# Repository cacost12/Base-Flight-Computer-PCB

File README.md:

<h1>Flight Computer Lite</h1>

<p><b>Current PCB Revision:</b> 1.0</p>
<p><b>PCB Part Number:</b> A0007</p>

<p>The Avionics team aims to produce a dual-deploy flight computer 
 for use in high powered rocketry projects. The Avionics
flight computer PCB uses an ARM Microcontroller to provide a 
computationally capable embedded protoyping 
platform for high powered rocketry projects with minimal wiring and a small
 form factor.</p>

<b>Working Directory Structure:</b>
 
 <p>
doc: documentation
    
src: source design files, e.g. schematic and board files
 
lib: libraries for schematic symbols and footprints
 
production: files needed for pcb fabrication, e.g. gerbers, profile, drill file
 
 sim: simulation files 
  
 cad: 3d models
   
 img: images of circuit/footprints for github display 
 </p>

<h2>3D Model: </h2>

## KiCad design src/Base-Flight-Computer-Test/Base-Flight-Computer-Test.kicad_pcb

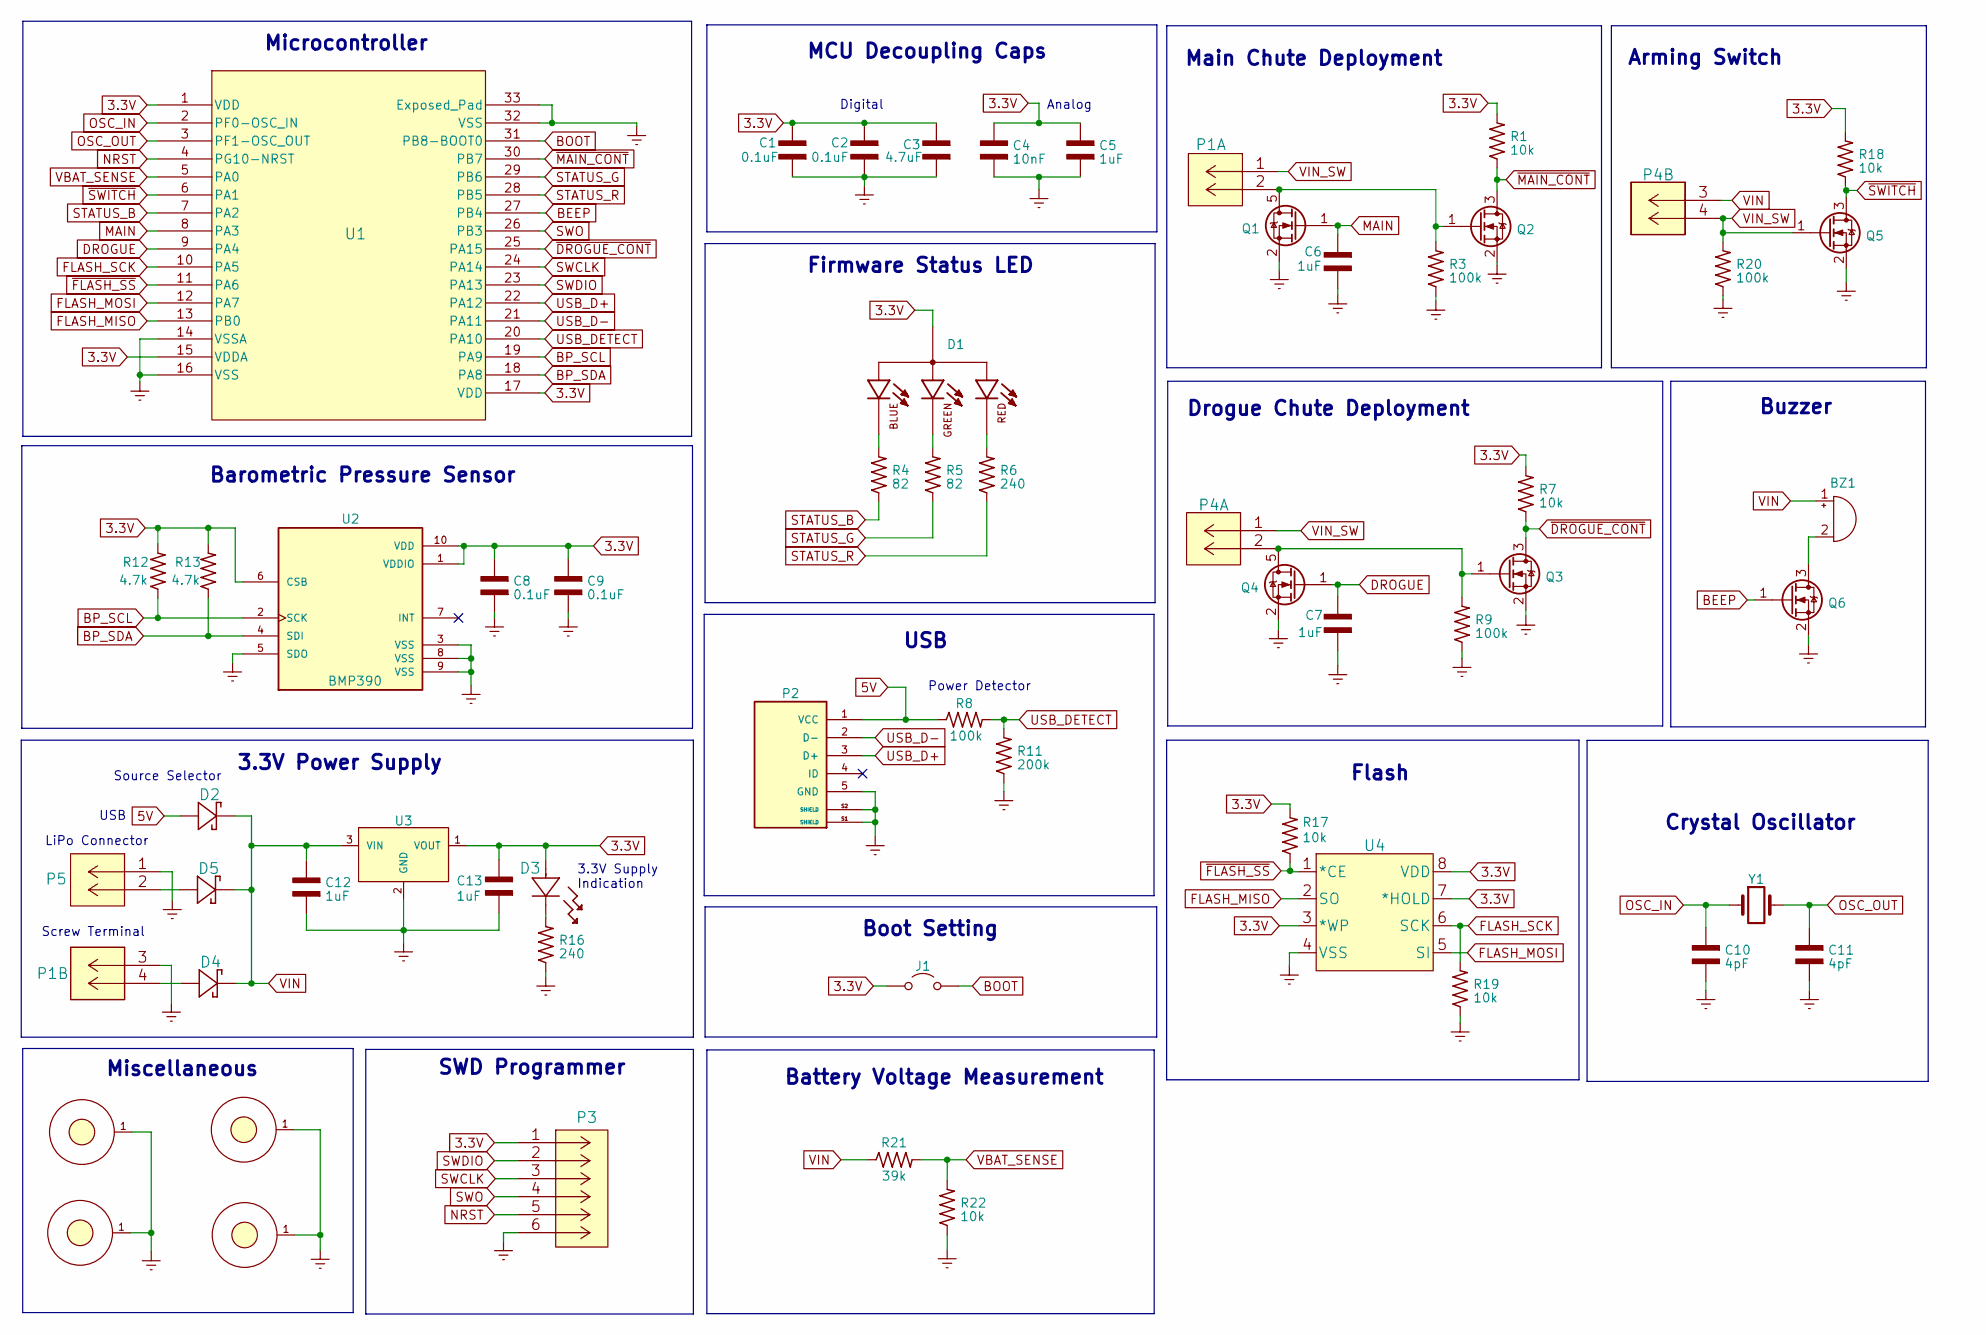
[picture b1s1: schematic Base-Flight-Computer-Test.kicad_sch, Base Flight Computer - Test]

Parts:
BZ1: AT-1438-TWT-R
C1, C2, C8, C9: 0.1uF; CAP_0402
C3: 4.7uF; CAP_0402
C4: 10nF; CAP_0402
C5, C6, C7: 1uF; CAP_0402
C10, C11: 4pF; CAP_0402
C12, C13: 1uF; CAP_0603
D1: CLMVC-FKA-CL1D1L71BB7C3C3
D2, D4, D5: PMEG3010AESBYL
D3: LTST-C191KGKT
H1, H2, H3, H4: Mounting-Hole-4-40; MountingHole_4-40
J1: Jumper_NO; Jumper-NO
P1, P4: 1984659; 1546551-4
P2: USB; 10118194-0001LF
P3: 0530470610; 53047-0610
P5: B2B-PH-K-SLFSN_JST
Q1, Q4: QS5U17TR
Q2, Q3, Q5, Q6: 2N7002W-7-F
R1, R7, R17, R18, R19, R22: 10k; RES_0402
R3, R8, R9, R20: 100k; RES_0402
R4, R5: 82; RES_0402
R6, R16: 240; RES_0402
R11: 200k; RES_0402
R12, R13: 4.7k; RES_0402
R21: 39k; RES_0402
U1: STM32G4A1KEU6
U2: BMP390
U3: LMS8117AMP-3.3_NOPB; AP7370-33Y-13
U4: SST25VF040B-50-4I-S2AE-T
Y1: ECS-240-18-33-JGN-TR; ECS-240-12-37B-CKY-TR

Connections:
3.3V: C1.1, C2.1, C3.1, C4.1, C5.1, C8.1, C9.1, C13.1, D1.1, D3.2, J1.1 (A), P3.1, R1.2, R7.2, R12.2, R13.2, R17.2, R18.2, U1.1 (VDD), U1.15 (VDDA), U1.17 (VDD), U2.1 (VDDIO), U2.6 (CSB), U2.10 (VDD), U3.1 (VOUT), U4.3 (*WP), U4.7 (*HOLD), U4.8 (VDD)
5V: D2.A, P2.1 (VCC), R8.1
BEEP: Q6.1 (G), U1.27 (PB4)
BOOT: J1.2 (B), U1.31 (PB8-BOOT0)
BP_SCL: R12.1, U1.19 (PA9), U2.2 (SCK)
BP_SDA: R13.1, U1.18 (PA8), U2.4 (SDI)
DROGUE: C7.1, Q4.1 (G), U1.9 (PA4)
Earth: C1.2, C2.2, C3.2, C4.2, C5.2, C6.2, C7.2, C8.2, C9.2, C10.2, C11.2, C12.2, C13.2, H1.1, H2.1, H3.1, H4.1, P1.3 (5), P2.5 (GND), P2.S1 (SHIELD), P2.S2 (SHIELD), P3.6, P5.1 (5), Q1.2 (S), Q2.2 (S), Q3.2 (S), Q4.2 (S), Q5.2 (S), Q6.2 (S), R3.1, R9.1, R11.1, R16.1, R19.1, R20.1, R22.1, U1.14 (VSSA), U1.16 (VSS), U1.32 (VSS), U1.33 (Exposed_Pad), U2.3 (VSS), U2.5 (SDO), U2.8 (VSS), U2.9 (VSS), U3.2 (GND), U4.4 (VSS)
FLASH_MISO: U1.13 (PB0), U4.2 (SO)
FLASH_MOSI: U1.12 (PA7), U4.5 (SI)
FLASH_SCK: R19.2, U1.10 (PA5), U4.6 (SCK)
MAIN: C6.1, Q1.1 (G), U1.8 (PA3)
NRST: P3.5, U1.4 (PG10-NRST)
unnamed: BZ1.2 (+), Q6.3 (D)
unnamed: D1.2, R4.2
unnamed: D1.3, R5.2
unnamed: D1.4, R6.2
unnamed: D3.1, R16.2
unnamed: P1.2 (6), Q1.5 (D), Q2.1 (G), R3.2
unnamed: D4.A, P1.4 (6)
unnamed: P4.2 (6), Q3.1 (G), Q4.5 (D), R9.2
unnamed: D5.A, P5.2 (6)
OSC_IN: C10.1, U1.2 (PF0-OSC_IN), Y1.1
OSC_OUT: C11.1, U1.3 (PF1-OSC_OUT), Y1.3
STATUS_B: R4.1, U1.7 (PA2)
STATUS_G: R5.1, U1.29 (PB6)
STATUS_R: R6.1, U1.28 (PB5)
SWCLK: P3.3, U1.24 (PA14)
SWDIO: P3.2, U1.23 (PA13)
SWO: P3.4, U1.26 (PB3)
USB_D+: P2.3 (D+), U1.22 (PA12)
USB_D-: P2.2 (D-), U1.21 (PA11)
USB_DETECT: R8.2, R11.2, U1.20 (PA10)
VBAT_SENSE: R21.2, R22.2, U1.5 (PA0)
VIN: BZ1.1 (-), C12.1, D2.C, D4.C, D5.C, P4.3 (5), R21.1, U3.3 (VIN)
VIN_SW: P1.1 (5), P4.1 (5), P4.4 (6), Q5.1 (G), R20.2
~DROGUE_CONT: Q3.3 (D), R7.1, U1.25 (PA15)
~FLASH_SS: R17.1, U1.11 (PA6), U4.1 (*CE)
~MAIN_CONT: Q2.3 (D), R1.1, U1.30 (PB7)
~SWITCH: Q5.3 (D), R18.1, U1.6 (PA1)

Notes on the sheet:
MCU Decoupling Caps
Drogue Chute Deployment
Flash
Digital
USB
Source Selector
Analog
Barometric Pressure Sensor
LiPo Connector
3.3V Supply Indication
Miscellaneous
Boot Setting
3.3V Power Supply
Main Chute Deployment
Firmware Status LED
Battery Voltage Measurement
Screw Terminal
Arming Switch
SWD Programmer
Buzzer
Microcontroller
Power Detector
Crystal Oscillator

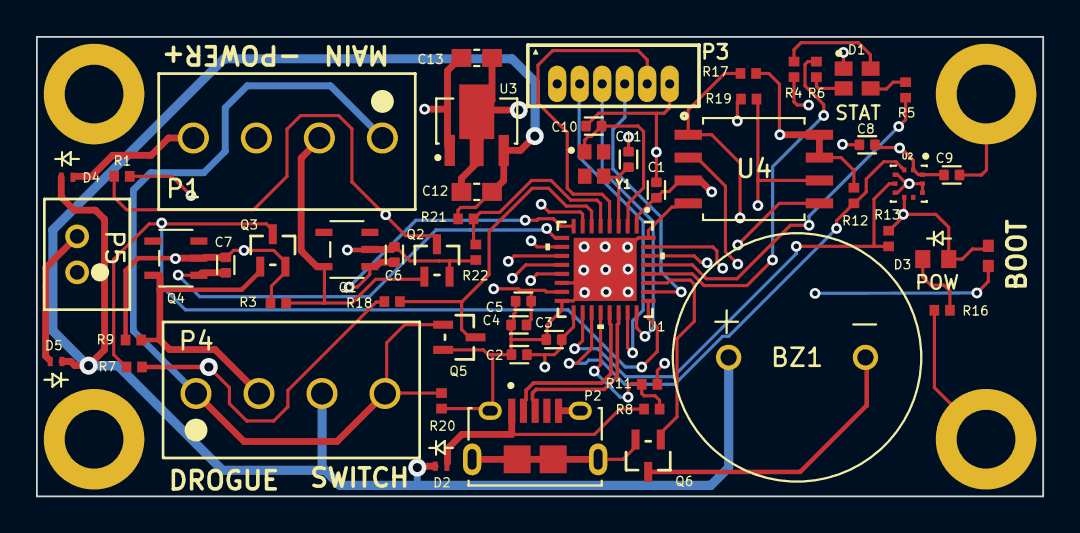
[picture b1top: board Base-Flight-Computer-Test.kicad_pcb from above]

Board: 4 copper layers, 55.9 x 25.5 mm, 58 parts (0 on the bottom side), 40 nets.

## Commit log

2022-12-17 created initial directory structure
2022-12-17 fixed README title
2022-12-17 fixed readme typo
2022-12-17 created initial footprint library
2022-12-17 created initial component symbol library
2022-12-17 completed schematic
2022-12-18 imported footprints into layout
2022-12-18 finalized board outline and component placements
2022-12-19 finalized rev1 routing
2022-12-19 resolved DRC errors
2022-12-19 generated gerbers files
2022-12-19 added PCB images to readme
2022-12-20 added ignition continuity pull down resistors to schematic
2022-12-21 added ignition pull down resistors to layout
2023-02-01 reduced form factor
2023-02-02 re-routed PCB to smaller form factor
2023-02-02 generated fabrication outputs
2023-02-06 kicad backups
2023-03-04 added new mcu to lib files
2023-03-05 created rev2 schematic
2023-03-05 placed rev2 components on board
2023-03-23 began PCB routing
2023-03-24 finished initial routing
2023-05-19 removed programming button
2023-05-19 increased blue LED resistance
2023-05-19 copied over component symbols from sdr library
2023-05-19 added 0402 resistor to component symbol library
2023-05-19 moved symbol library to lib directory
2023-05-19 removed sdr flight computer lite symbol library
2023-05-19 created new footprint library
2023-05-19 added 0402 resistor to footprint library
2023-05-19 updated footprint library
2023-05-19 added 4-40 screw mounting hole to component libraries
2023-05-20 linked all component symbols to footprints
2023-05-20 updated schematic links to new library files
2023-05-20 added new 6 terminal screw terminal to lib files
2023-05-20 added new screw terminals to schematic
2023-05-20 added LiPo connector to lib files
2023-05-20 added 0402 capacitor to lib files
2023-05-20 updated schematic with 0402 resistors and capacitors
2023-05-20 added battery measurement circuit
2023-05-20 added new linear regulator to lib files
2023-05-21 swapped out linear regulator for reduced form factor
2023-05-21 removed extra units from JST connector symbol
2023-05-21 added lipo batter connector to power supply circuit
2023-05-21 reduced form factor of crystal oscillator
2023-05-21 changed ignition pull-down resistors to 100k to reduce parasitic ematch current
2023-05-21 moved all components to single schematic page
2023-05-21 updated symbol footprint links in schematic
2023-05-21 added four terminal screw terminal to lib files
2023-05-21 replaced green power indication LED with smaller 0603 alternate
2023-05-21 replaced schottky diode with smaller form factor diode
2023-05-22 swapped out 90 degree LiPo connector for straight connector
2023-05-24 finished placing components on board
2023-05-26 created new project for preliminary hardware testing
2023-05-26 placed components on test board
2023-05-26 updated DRC ruleset
2023-05-26 completed initial test layout
2023-05-27 resolved DRC issues with Test layout
2023-05-27 generated test board gerber files
2023-05-27 plotted schematic
2023-06-02 organized production folder and generated BOM
2023-07-30 Generated step file
